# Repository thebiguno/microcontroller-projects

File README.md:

microcontroller-projects
========================

A home for my microcontroller projects, including Stubby the Hexapod and others.  It includes libraries for avr-gcc along with sample programs on how to use them, some KiCad modules, and the source code for a number of projects.

Some major projects include:
 * Stubby the Hexapod (http://stubby.digitalcave.ca/stubby/) (Now extracted into its own repo at https://github.com/thebiguno/stubby)
 * DrumMaster (http://drummaster.digitalcave.ca/drummaster/)
 * Chiindii (http://chiindii.digitalcave.ca/chiindii/)

Some of the AVR libraries included here are:
 * serial communications
 * TWI (I2C), with support for master read / master write / slave read / slave write, plus callback functions for asyncronous communications
 * reading data from a PS2 controller
 * timer functions
 * and much more

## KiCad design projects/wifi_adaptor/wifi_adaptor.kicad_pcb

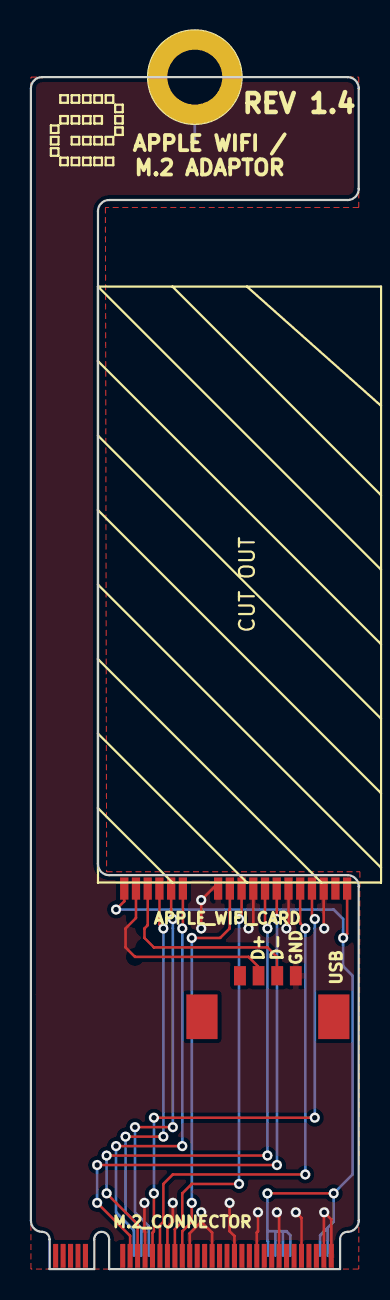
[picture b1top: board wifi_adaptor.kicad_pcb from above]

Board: 2 copper layers, 22.0 x 80.0 mm, 5 parts (0 on the bottom side), 13 nets.

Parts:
J1: APPLE_WIFI_CARD
J2: m.2_connector; M.2_CONNECTOR
MP1: MOUNTING_HOLE; MOUNTING_HOLE_#6
MP2: GRAPHIC; DIGITALCAVE_LOGO
P1: USB; Pin_Header_Straight_1x04

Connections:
+3V3: J1.1, J1.18, J2.2, J2.4, J2.12, J2.14, J2.16, J2.18
GND: J1.3, J1.6, J1.9, J1.12, J2.1, J2.3, J2.9, J2.15, J2.21, J2.27, J2.33, J2.39, J2.45, J2.51, MP1.1, P1.4
unnamed: J1.4, J2.49
unnamed: J1.5, J2.47
unnamed: J1.7, J2.55
unnamed: J1.8, J2.53
unnamed: J1.10, J2.43
unnamed: J1.11, J2.41
unnamed: J1.13, J2.54
unnamed: J1.14, J2.50
unnamed: J1.15, J2.52
unnamed: J1.16, P1.3
unnamed: J1.17, P1.2

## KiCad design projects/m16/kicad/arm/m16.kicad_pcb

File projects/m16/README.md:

https://esdblog.org/how-to-drive-4096-rgb-leds-each-24bit-rgb-brightness-with-one-stm32-microcontroller-without-much-cpu-load/

4-bits per pixel, expanding to 16-bit per pixel for gamma adjustment
see http://www.batsocks.co.uk/readme/p_art_bcm.htm
0     0
1    17/32767 = 0.0005%
2   116
3   362
4   809
5  1512
6  2519
7  3878
8  5637
9  7839
a 10529
b 13749
c 17542
d 21949
e 27011
f 32767

64x32 matrix w/ 1/16 scan rate
2048 rgb leds, 16 * 128 rgb rows

3072 byte frame buffer ?
dma buffer: [x:x:x:b1:g1:r1:ck:b0:g0:r0:oe:st:d:c:b:a] ?
2 rgb leds per dma value
64 dma values per row
16384 16-bit dma values per frame

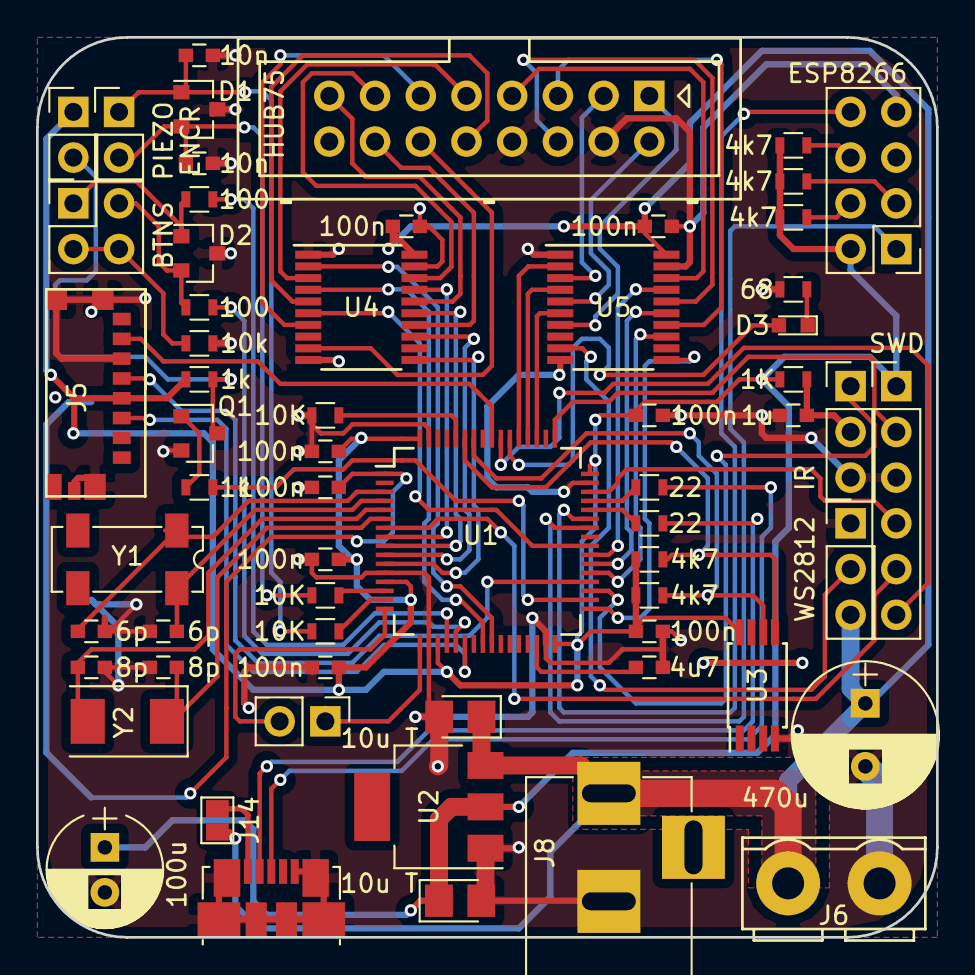
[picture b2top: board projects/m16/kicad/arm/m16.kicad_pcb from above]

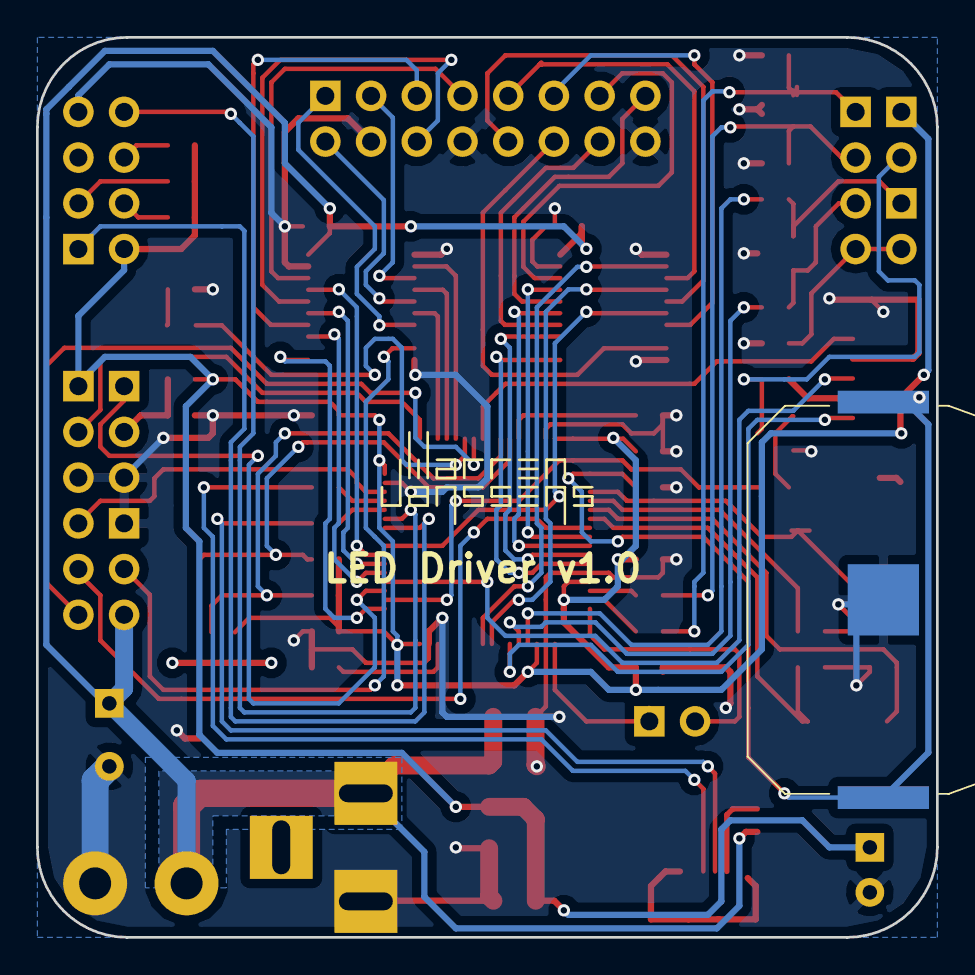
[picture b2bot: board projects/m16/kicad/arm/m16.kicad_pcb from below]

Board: 2 copper layers, 50.0 x 50.0 mm, 64 parts (2 on the bottom side), 75 nets.

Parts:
BT1: 2032 3V; Keystone_3034_1x20mm-CoinCell
C1, C3: 10n; C_0603
C2, C4, C8, C9, C10, C11, C12, C17: 100n; C_0603
C5, C7: 6p; C_0603
C6: 4u7; C_0603
C13: 470u; CP_Radial_D8.0mm_P3.50mm
C14, C16: 10u T; CP_Tantalum_Case-R_EIA-2012-12_Reflow
C15: 1u; C_0603
C18: 100u; CP_Radial_D6.3mm_P2.50mm
C19, C20: 8p; C_0603
D1, D2: D_TVS_x2_AAC; SOT-23
D3: LED; LED_0603
J1: ENCR; Pin_Header_Straight_1x02_Pitch2.54mm
J2: SWD; Pin_Header_Straight_1x06_Pitch2.54mm
J3: BTNS; Pin_Header_Straight_2x02_Pitch2.54mm
J4: ESP8266; Pin_Header_Straight_2x04_Pitch2.54mm
J5: Molex 475710001; 475710001
J6: Conn_01x02; SCREW_TERMINAL_2
J7: HUB75; Multicomp_MC9A12-1634_2x08x2.54mm_Straight
J8: POWER; BARREL_JACK
J9: PIEZO; Pin_Header_Straight_1x02_Pitch2.54mm
J10: IR; Pin_Header_Straight_1x03_Pitch2.54mm
J11: WS2812; Pin_Header_Straight_1x03_Pitch2.54mm
J12: USB_OTG; USB_Micro-B_Molex_47346-0001
J13: SERIAL; Pin_Header_Straight_1x02_Pitch2.54mm
J14: GS2
Q1: MMBT3904; SOT-23
R1, R3, R9: 10K; R_0603
R2, R4: 1k; R_0603
R5, R15: 100; R_0603
R6, R7, R8, R13, R14: 4k7; R_0603
R10: 68; R_0603
R11: 1K; R_0603
R12, R17: 22; R_0603
R16: 10k; R_0603
U1: STM32F411RETx; LQFP-64_10x10mm_Pitch0.5mm
U2: LM1117-3.3; SOT-223
U3: 24LC16; TSSOP-8_4.4x3mm_Pitch0.65mm
U4, U5: 74HCT244; TSSOP-20_4.4x6.5mm_Pitch0.65mm
WJ20: VAL**; WJ20
Y1: ABS25-32.768-6; Crystal_SMD_SeikoEpson_MC306-4pin_8.0x3.2mm
Y2: 16MHz; Crystal_SMD_0603-2pin_6.0x3.5mm

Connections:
+3V3: C8.2, C9.2, C10.2, C11.2, C12.2, C16.1, C18.1, J2.1, J4.2, J5.4, J9.1, R4.1, R6.1, R7.1, R8.1, R11.2, R13.1, R14.2, U1.13, U1.19, U1.32, U1.48, U1.64, U2.2, U3.8
+5V: C2.2, C13.1, C14.1, C17.2, J6.1, J8.1, J11.3, J14.2, U2.3, U4.20, U5.20
+BATT: BT1.1, C4.1, U1.1
/EN1_A: R3.2, U1.14
/EN1_B: R1.2, U1.15
/ESP_EN: J4.6, R8.2
/ESP_RX: J4.1, U1.42
/ESP_TX: J4.8, U1.43
/HSE_N: C19.1, U1.6, Y2.1
/HSE_P: C20.1, U1.5, Y2.2
/IDC_A: J7.9, U4.3
/IDC_B: J7.10, U4.5
/IDC_B0: J7.3, U5.3
/IDC_B1: J7.7, U5.18
/IDC_C: J7.11, U4.7
/IDC_CLK: J7.13, U4.18
/IDC_D: J7.12, U4.9
/IDC_G0: J7.2, U5.5
/IDC_G1: J7.6, U5.16
/IDC_OE: J7.15, U4.16
/IDC_R0: J7.1, U5.7
/IDC_R1: J7.5, U5.14
/IDC_STB: J7.14, U4.14
/IR_DO: J10.1, U1.35
/IR_VS: C15.2, J10.2, R11.1
/JTCK: J2.2, U1.49
/JTMS: J2.4, U1.46
/LED: D3.2, U1.54
/LSE_N: C7.1, U1.4, Y1.4
/LSE_P: C5.1, U1.3, Y1.1
/NRST: J2.5, U1.7
/PZ_DO: R2.1, U1.34
/RGB_A: U1.8, U4.17
/RGB_B: U1.9, U4.15
/RGB_B0: U1.39, U5.17
/RGB_B1: U1.53, U5.2
/RGB_C: U1.10, U4.13
/RGB_CLK: U1.25, U4.2
/RGB_D: U1.11, U4.11
/RGB_G0: U1.38, U5.15
/RGB_G1: U1.52, U5.4
/RGB_OE: U1.24, U4.4
/RGB_R0: U1.37, U5.13
/RGB_R1: U1.51, U5.6
/RGB_STB: U1.40, U4.6
/RX: J13.1, U1.17
/SCL: R14.1, U1.58, U3.6
/SDA: R13.2, U1.59, U3.5
/SDIO_CK: J5.5, U1.36
/SDIO_CMD: J5.3, U1.22
/SDIO_D0: J5.7, U1.56
/SW1: R5.1, U1.20
/SW2: R15.1, U1.21
/SWO: J2.6, U1.55
/TX: J13.2, U1.16
/USB_DM: R17.2, U1.44
/USB_DP: R12.2, U1.45
/WS_DI: J11.2, U5.9
/WS_DO: U1.33, U5.11
GND: BT1.2, C1.1, C2.1, C3.1, C4.2, C5.2, C6.2, C7.2, C8.1, C9.1, C10.1, C11.1, C12.1, C13.2, C14.2, C15.1, C16.2, C17.1, C18.2, C19.2, C20.2, D1.3, D2.3, J2.3, J4.7, J5.6, J5.9, J5.10, J5.11, J5.12, J6.2, J7.4, J7.8, J7.16, J8.2, J10.3, J11.1, J12.5, J12.6, Q1.2, R9.2, R10.2, R16.1, U1.12, U1.18, U1.31, U1.47, U1.63, U2.1, U3.4, U4.1, U4.10, U4.19, U5.1, U5.10, U5.19
unnamed: C1.2, D1.1, J1.1, R1.1
unnamed: C3.2, D1.2, J1.2, R3.1
unnamed: C6.1, U1.30
unnamed: D2.1, J3.1, R5.2
unnamed: D2.2, J3.2, R15.2
unnamed: D3.1, R10.1
unnamed: J3.3, J3.4, R16.2
unnamed: J4.3, R6.2
unnamed: J4.4, R7.2
unnamed: J9.2, Q1.3, R4.2
unnamed: J12.1, J14.1
unnamed: J12.2, R17.1
unnamed: J12.3, R12.1
unnamed: Q1.1, R2.2
unnamed: R9.1, U1.60

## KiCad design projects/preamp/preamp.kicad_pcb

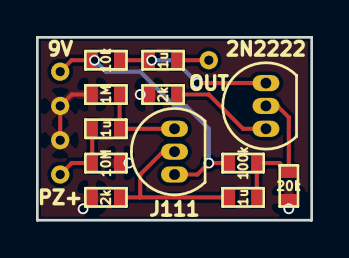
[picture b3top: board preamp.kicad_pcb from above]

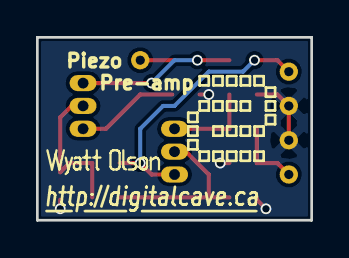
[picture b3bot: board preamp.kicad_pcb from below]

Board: 2 copper layers, 15.2 x 10.2 mm, 18 parts (3 on the bottom side), 9 nets.

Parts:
C1, C2, C3: 1u; SM0603_VALUE
MP1: GRAPHIC; DIGITALCAVE_AUTHOR
MP2: GRAPHIC; DIGITALCAVE_LOGO
MP3: GRAPHIC; DIGITALCAVE_URL
P1: PZ+; Pin_Header_Straight_1x02
P2: 9V; Pin_Header_Straight_1x02
P4: OUT; Pin_Header_Straight_1x01
Q1: J111; TO-92_Inline_Narrow_Oval
Q2: 2N2222; TO-92_Inline_Narrow_Oval
R1: 10M; SM0603_VALUE
R2: 1M; SM0603_VALUE
R3, R7: 2k; SM0603_VALUE
R4: 100k; SM0603_VALUE
R5: 20k; SM0603_VALUE
R6: 10k; SM0603_VALUE

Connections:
+BATT: P2.1, Q1.1, R4.1, R6.1
GND: P1.2, P2.2, R1.2, R2.2, R3.2, R5.2, R7.2
unnamed: C1.1, Q1.3, R2.1
unnamed: C1.2, P1.1, R1.1
unnamed: C2.1, Q2.2, R4.2, R5.1
unnamed: C2.2, Q1.2, R3.1
unnamed: C3.1, P4.1
unnamed: C3.2, Q2.3, R6.2
unnamed: Q2.1, R7.1

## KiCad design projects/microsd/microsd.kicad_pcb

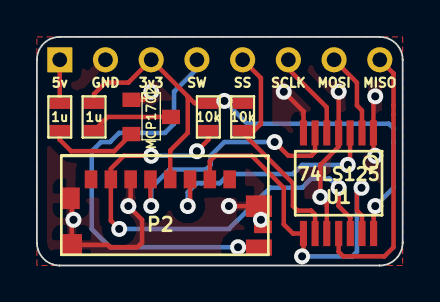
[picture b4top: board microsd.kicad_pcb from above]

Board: 2 copper layers, 20.3 x 12.7 mm, 8 parts (0 on the bottom side), 14 nets.

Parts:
C1, C2: 1u; SM0603_VALUE
P1: CONN_8; SIL-8
P2: CONN_13; 475710001
R1, R2: 10k; SM0603_VALUE
U1: 74LS125; SSOP-14
VR1: MCP1702; SOT23

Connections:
/5V: C2.2, P1.1
/CLK: P2.5, U1.6
/CS: P2.2, U1.8, U1.13
/DET: P1.4, P2.13
/DI: P2.3, U1.3
/DO: P2.7, R1.1, U1.12
/MISO: P1.8, U1.11
/MOSI: P1.7, U1.2
/SCLK: P1.6, U1.5
/SS: P1.5, R2.2, U1.9
GND: P1.2, P2.6, P2.9, P2.10, P2.11, P2.12, U1.1, U1.4, U1.7, U1.10, VR1.1
unnamed: C2.1, VR1.2
unnamed: C1.1, VR1.3
VCC: C1.2, P1.3, P2.4, R1.2, R2.1, U1.14

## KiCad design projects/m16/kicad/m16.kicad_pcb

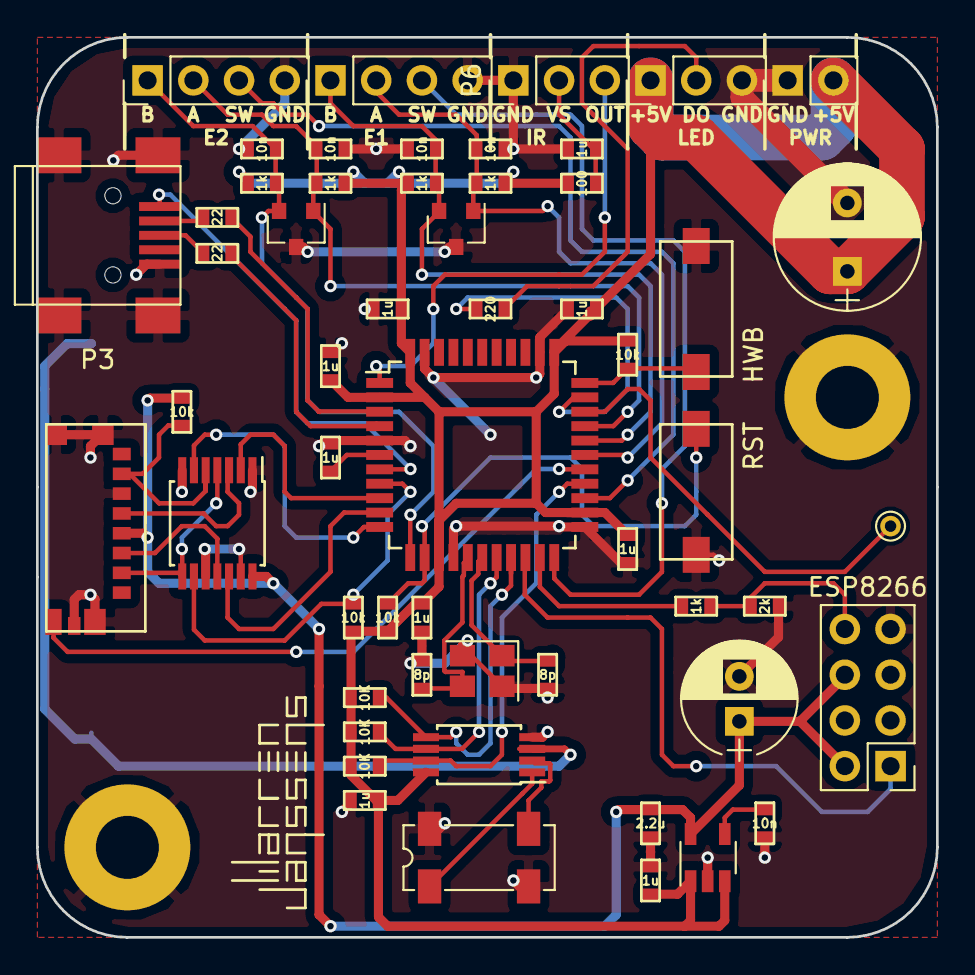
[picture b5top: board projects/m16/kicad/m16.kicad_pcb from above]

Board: 2 copper layers, 50.0 x 50.0 mm, 59 parts (1 on the bottom side), 43 nets.

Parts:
BT1: 3V; Keystone_3034_1x20mm-CoinCell
C1, C2, C3, C4, C19: 10n; SM0603_VALUE
C5, C6: 8p; SM0603_VALUE
C7, C8, C9, C10, C11, C12, C13, C15, C18: 1u; SM0603_VALUE
C14: 470u; CP_Radial_D8.0mm_P3.80mm
C16: 100u; CP_Radial_D6.3mm_P2.50mm
C17: 2.2u; SM0603_VALUE
D1, D2: TVS; SOT-23
J2: TEST_1P; PINTST
MP1, MP2: MOUNTING_HOLE; MountingHole_3.5mm_Pad
P1: ENC1; Pin_Header_Straight_1x04_Pitch2.54mm
P2: ENC2; Pin_Header_Straight_1x04_Pitch2.54mm
P3: USB_OTG; USB_Mini-B
P4: Molex 475710001; 475710001
P5: PWR; Pin_Header_Straight_1x02_Pitch2.54mm
P6: IR; Pin_Header_Straight_1x03_Pitch2.54mm
P7: ESP8266; Pin_Header_Straight_2x04_Pitch2.54mm
P8: WS2812; Pin_Header_Straight_1x03_Pitch2.54mm
R1, R2, R3, R4, R14: 1k; SM0603_VALUE
R5, R6, R7, R11: 10k; SM0603_VALUE
R8, R9: 22; SM0603_VALUE
R10, R12, R13: 10K; SM0603_VALUE
R15: 2k; SM0603_VALUE
R16: 220; SM0603_VALUE
R17: 100; SM0603_VALUE
SW1: RST; SW_6x3
SW2: HWB; SW_6x3
U1: 74LS125; TSSOP-14_4.4x5mm_Pitch0.65mm
U2: ATMEGA32U4-A; TQFP-44_10x10mm_Pitch0.8mm
U3: MCP7941X; TSSOP-8_4.4x3mm_Pitch0.65mm
U4: MIC5219-3.3BM5; TSOT-23-5
WJ20: VAL**; WJ20
X1: 16M 8p; Crystal_SMD_3225-4pin_3.2x2.5mm
X2: 32.768k 6-9p; Crystal_SMD_SeikoEpson_MC306-4pin_8.0x3.2mm

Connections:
+3V3: C16.1, C17.1, P4.4, P7.2, P7.6, R5.1, U1.14, U4.5
+5V: C8.1, C9.1, C10.1, C11.1, C12.1, C13.1, C14.1, C15.1, P5.2, P8.1, R1.2, R2.2, R3.2, R4.2, R6.1, R7.1, R10.1, R11.2, R12.1, R13.1, R17.2, U2.2, U2.14, U2.24, U2.34, U2.44, U3.8, U4.1, U4.3
+BATT: BT1.1, U3.3
/CLK: P4.5, U1.3
/CS: P4.2, U1.4, U1.8
/D+: R8.2, U2.4
/D-: R9.2, U2.3
/DET: P4.13, U2.27
/DI: P4.3, U1.11
/DN: P3.2, R9.1
/DO: P4.7, R5.2, U1.5
/DP: P3.3, R8.1
/E1A: C1.2, D1.1, P1.2, R1.1, U2.28
/E1B: C3.2, D1.2, P1.1, R3.1, U2.29
/E1S: P1.3, U2.22
/E2A: C2.2, D2.1, P2.2, R2.1, U2.30
/E2B: C4.2, D2.2, P2.1, R4.1, U2.12
/E2S: P2.3, U2.25
/HWB: R11.1, SW2.1, U2.33
/IROUT: P6.3, U2.1
/LED: R16.2, U2.32
/MFP: R13.2, U2.26, U3.7
/MISO: U1.6, U2.11
/MOSI: U1.12, U2.10
/RST: R7.2, SW1.2, U2.13
/RX_TX: P7.1, U2.20
/SCL: R10.2, U2.18, U3.6
/SCLK: U1.2, U2.9
/SDA: R12.2, U2.19, U3.5
/SS: R6.2, U1.9, U2.8
/TX_RX: R14.2, U2.21
/VBUS: P3.1, U2.7
/X+: C5.2, U2.17, X1.1
/X-: C6.2, U2.16, X1.3
/Y+: U3.1, X2.1
/Y-: U3.2, X2.3
GND: BT1.2, C1.1, C2.1, C3.1, C4.1, C5.1, C6.1, C7.1, C8.2, C9.2, C10.2, C11.2, C12.2, C13.2, C14.2, C15.2, C16.2, C17.2, C18.1, C19.2, D1.3, D2.3, MP1.1, MP2.1, P1.4, P2.4, P3.5, P3.6, P4.6, P4.9, P4.10, P4.11, P4.12, P5.1, P6.1, P7.7, P8.3, R15.1, SW1.1, SW2.2, U1.1, U1.7, U1.10, U1.13, U2.5, U2.15, U2.23, U2.35, U2.43, U3.4, U4.2, X1.2, X1.4, X2.2, X2.4
unnamed: C7.2, U2.6
unnamed: C18.2, P6.2, R17.1
unnamed: C19.1, U4.4
unnamed: J2.1, U2.31
unnamed: P7.8, R14.1, R15.2
unnamed: P8.2, R16.1

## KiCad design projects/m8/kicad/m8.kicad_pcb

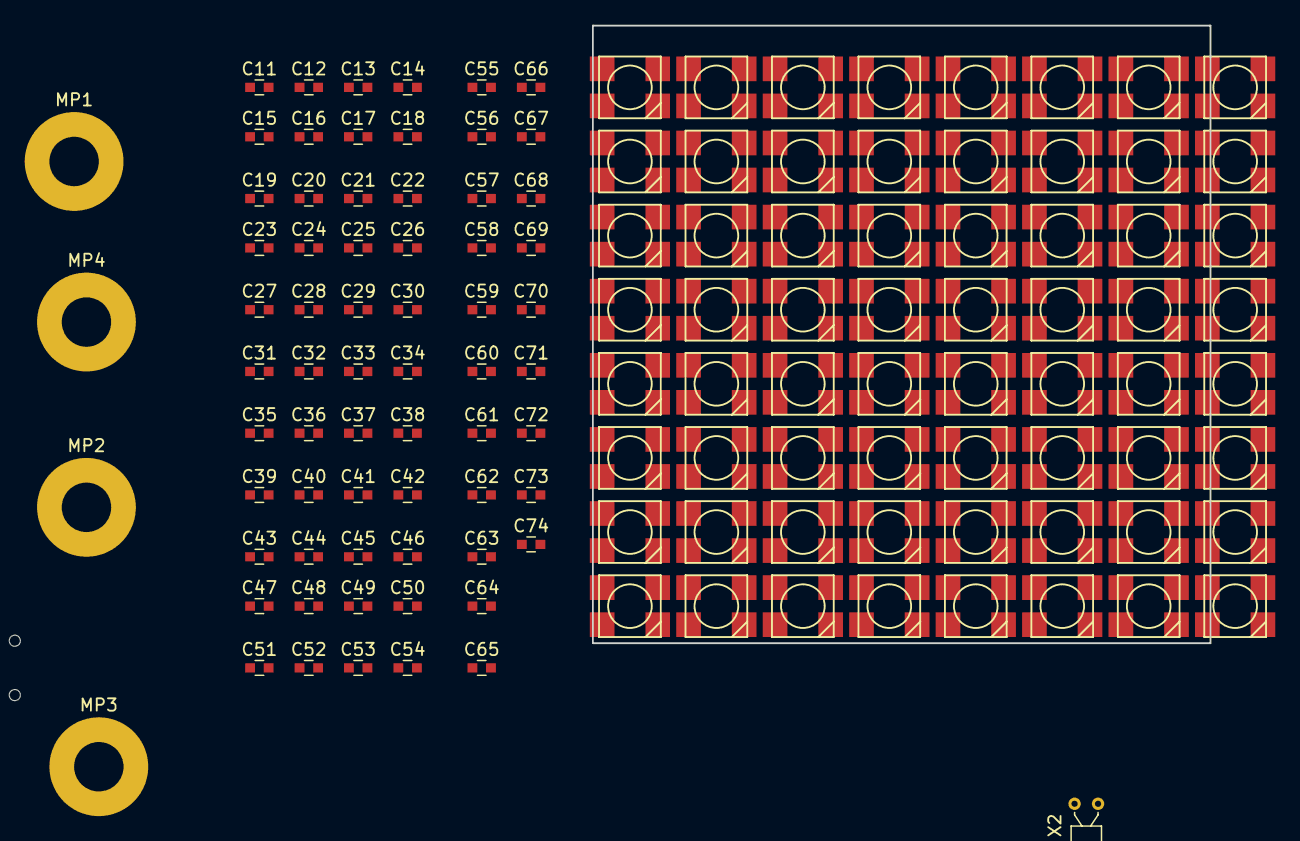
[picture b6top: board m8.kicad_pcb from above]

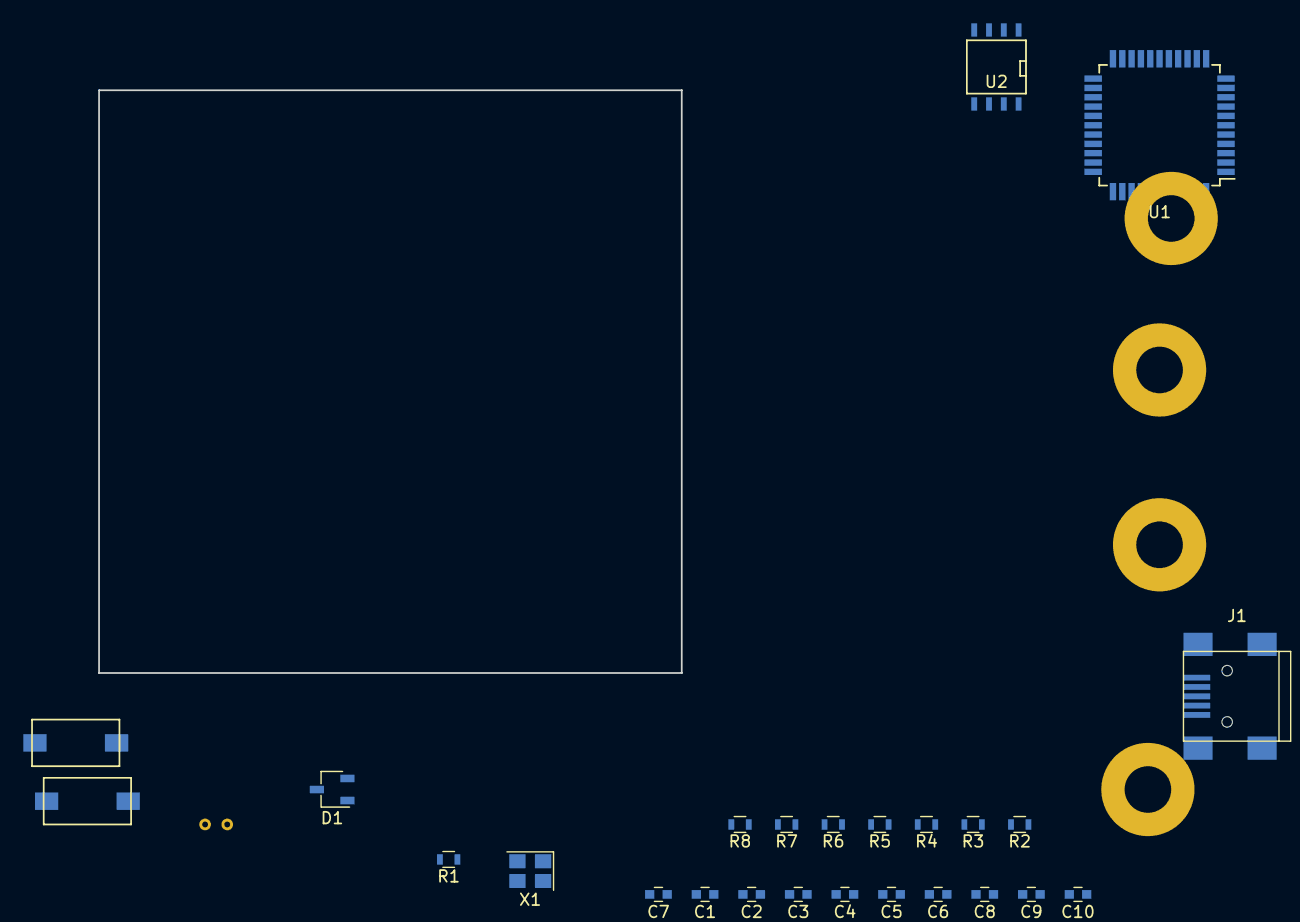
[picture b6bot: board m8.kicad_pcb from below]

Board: 2 copper layers, 50.0 x 50.0 mm, 158 parts (25 on the bottom side), 83 nets, no tracks yet.

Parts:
C1, C2: 12pF; C_0603
C3: 1uF; C_0603
C4, C11, C12, C13, C14, C15, C16, C17, C18, C19, C20, C21, C22, C23, C24, C25, C26, C27, C28, C29, C30, C31, C32, C33, C34, C35, C36, C37, C38, C39, C40, C41, C42, C43, C44, C45, C46, C47, C48, C49, C50, C51, C52, C53, C54, C55, C56, C57, C58, C59, C60, C61, C62, C63, C64, C65, C66, C67, C68, C69, C70, C71, C72, C73, C74: 0.1uF; C_0603
C5, C6, C7, C8, C9, C10: .1 uF; C_0603
D1: TVS_BIDIRECTIONAL_2CH; TSOT-23
J1: USB_OTG; USB_Mini-B
MP1, MP2, MP3, MP4: MOUNTING_HOLE; MountingHole_4mm_Pad
R1, R2: 22; R_0603
R3, R4: 4k7; R_0603
R5, R6, R7, R8: 10k; R_0603
SW3: HWB; SW_6x3
SW4: RST; SW_6x3
U1: ATMEGA32U4-AU; TQFP-44_10x10mm_Pitch0.8mm
U2: MCP7940N; SOIC-8-N
U3, U4, U5, U6, U7, U8, U9, U10, U11, U12, U13, U14, U15, U16, U17, U18, U19, U20, U21, U22, U23, U24, U25, U26, U27, U28, U29, U30, U31, U32, U33, U34, U35, U36, U37, U38, U39, U40, U41, U42, U43, U44, U45, U46, U47, U48, U49, U50, U51, U52, U53, U54, U55, U56, U57, U58, U59, U60, U61, U62, U63, U64, U65, U66: WS2812; SK6812
X1: 16 MHz 12pF; Crystal_SMD_3225-4pin_3.2x2.5mm
X2: 32.768 kHz 12pF; Crystal_C26-LF_d2.1mm_l6.5mm_Horizontal

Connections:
/DI: U1.10, U3.4
/HWB: R7.2, SW3.2, U1.33
/MFP: U1.1, U1.26, U1.27, U2.7
/RST: R8.2, SW4.2, U1.13
/SCL: D1.2, R3.1, U1.18, U2.6
/SDA: D1.1, R4.1, U1.19, U2.5
/SW_A: R5.2, U1.41
/SW_B: R6.2, U1.40
/UDM: J1.2, R2.1
/UDP: J1.3, R1.1
GND: C1.2, C2.2, C3.1, C4.1, C5.2, C6.2, C7.2, C8.2, C9.2, C10.2, C11.1, C12.1, C13.1, C14.1, C15.1, C16.1, C17.1, C18.1, C19.1, C20.1, C21.1, C22.1, C23.1, C24.1, C25.1, C26.1, C27.1, C28.1, C29.1, C30.1, C31.1, C32.1, C33.1, C34.1, C35.1, C36.1, C37.1, C38.1, C39.1, C40.1, C41.1, C42.1, C43.1, C44.1, C45.1, C46.1, C47.1, C48.1, C49.1, C50.1, C51.1, C52.1, C53.1, C54.1, C55.1, C56.1, C57.1, C58.1, C59.1, C60.1, C61.1, C62.1, C63.1, C64.1, C65.1, C66.1, C67.1, C68.1, C69.1, C70.1, C71.1, C72.1, C73.1, C74.1, D1.3, J1.5, J1.6, SW3.1, SW4.1, U1.5, U1.15, U1.23, U1.35, U1.43, U2.4, U3.3, U4.3, U5.3, U6.3, U7.3, U8.3, U9.3, U10.3, U11.3, U12.3, U13.3, U14.3, U15.3, U16.3, U17.3, U18.3, U19.3, U20.3, U21.3, U22.3, U23.3, U24.3, U25.3, U26.3, U27.3, U28.3, U29.3, U30.3, U31.3, U32.3, U33.3, U34.3, U35.3, U36.3, U37.3, U38.3, U39.3, U40.3, U41.3, U42.3, U43.3, U44.3, U45.3, U46.3, U47.3, U48.3, U49.3, U50.3, U51.3, U52.3, U53.3, U54.3, U55.3, U56.3, U57.3, U58.3, U59.3, U60.3, U61.3, U62.3, U63.3, U64.3, U65.3, U66.3, X1.2, X1.4
unnamed: C1.1, U1.17, X1.1
unnamed: C2.1, U1.16, X1.3
unnamed: C3.2, U1.6
unnamed: C4.2, U1.42
unnamed: R1.2, U1.4
unnamed: R2.2, U1.3
unnamed: U2.1, X2.2
unnamed: U2.2, X2.1
unnamed: U3.2, U4.4
unnamed: U4.2, U5.4
unnamed: U5.2, U6.4
unnamed: U6.2, U7.4
unnamed: U7.2, U8.4
unnamed: U8.2, U9.4
unnamed: U10.2, U11.4
unnamed: U9.2, U10.4
unnamed: U11.2, U12.4
unnamed: U12.2, U13.4
unnamed: U13.2, U14.4
unnamed: U14.2, U15.4
unnamed: U15.2, U16.4
unnamed: U16.2, U17.4
unnamed: U17.2, U18.4
unnamed: U18.2, U19.4
unnamed: U19.2, U20.4
unnamed: U20.2, U21.4
unnamed: U21.2, U22.4
unnamed: U22.2, U23.4
unnamed: U23.2, U24.4
unnamed: U24.2, U25.4
unnamed: U25.2, U26.4
unnamed: U26.2, U27.4
unnamed: U27.2, U28.4
unnamed: U28.2, U29.4
unnamed: U29.2, U30.4
unnamed: U30.2, U31.4
unnamed: U31.2, U32.4
unnamed: U32.2, U33.4
unnamed: U33.2, U34.4
unnamed: U34.2, U35.4
unnamed: U35.2, U36.4
unnamed: U36.2, U37.4
unnamed: U37.2, U38.4
unnamed: U38.2, U39.4
unnamed: U39.2, U40.4
unnamed: U40.2, U41.4
unnamed: U41.2, U42.4
unnamed: U42.2, U43.4
unnamed: U43.2, U44.4
unnamed: U44.2, U45.4
unnamed: U45.2, U46.4
unnamed: U46.2, U47.4
unnamed: U47.2, U48.4
unnamed: U48.2, U49.4
unnamed: U49.2, U50.4
unnamed: U50.2, U51.4
unnamed: U51.2, U52.4
unnamed: U52.2, U53.4
unnamed: U53.2, U54.4
unnamed: U54.2, U55.4
unnamed: U55.2, U56.4
unnamed: U56.2, U57.4
unnamed: U57.2, U58.4
unnamed: U58.2, U59.4
unnamed: U59.2, U60.4
unnamed: U60.2, U61.4
unnamed: U61.2, U62.4
unnamed: U62.2, U63.4
unnamed: U63.2, U64.4
unnamed: U64.2, U65.4
unnamed: U65.2, U66.4
VCC: C5.1, C6.1, C7.1, C8.1, C9.1, C10.1, C11.2, C12.2, C13.2, C14.2, C15.2, C16.2, C17.2, C18.2, C19.2, C20.2, C21.2, C22.2, C23.2, C24.2, C25.2, C26.2, C27.2, C28.2, C29.2, C30.2, C31.2, C32.2, C33.2, C34.2, C35.2, C36.2, C37.2, C38.2, C39.2, C40.2, C41.2, C42.2, C43.2, C44.2, C45.2, C46.2, C47.2, C48.2, C49.2, C50.2, C51.2, C52.2, C53.2, C54.2, C55.2, C56.2, C57.2, C58.2, C59.2, C60.2, C61.2, C62.2, C63.2, C64.2, C65.2, C66.2, C67.2, C68.2, C69.2, C70.2, C71.2, C72.2, C73.2, C74.2, J1.1, R3.2, R4.2, R5.1, R6.1, R7.1, R8.1, U1.2, U1.7, U1.14, U1.24, U1.34, U1.44, U2.8, U3.1, U4.1, U5.1, U6.1, U7.1, U8.1, U9.1, U10.1, U11.1, U12.1, U13.1, U14.1, U15.1, U16.1, U17.1, U18.1, U19.1, U20.1, U21.1, U22.1, U23.1, U24.1, U25.1, U26.1, U27.1, U28.1, U29.1, U30.1, U31.1, U32.1, U33.1, U34.1, U35.1, U36.1, U37.1, U38.1, U39.1, U40.1, U41.1, U42.1, U43.1, U44.1, U45.1, U46.1, U47.1, U48.1, U49.1, U50.1, U51.1, U52.1, U53.1, U54.1, U55.1, U56.1, U57.1, U58.1, U59.1, U60.1, U61.1, U62.1, U63.1, U64.1, U65.1, U66.1

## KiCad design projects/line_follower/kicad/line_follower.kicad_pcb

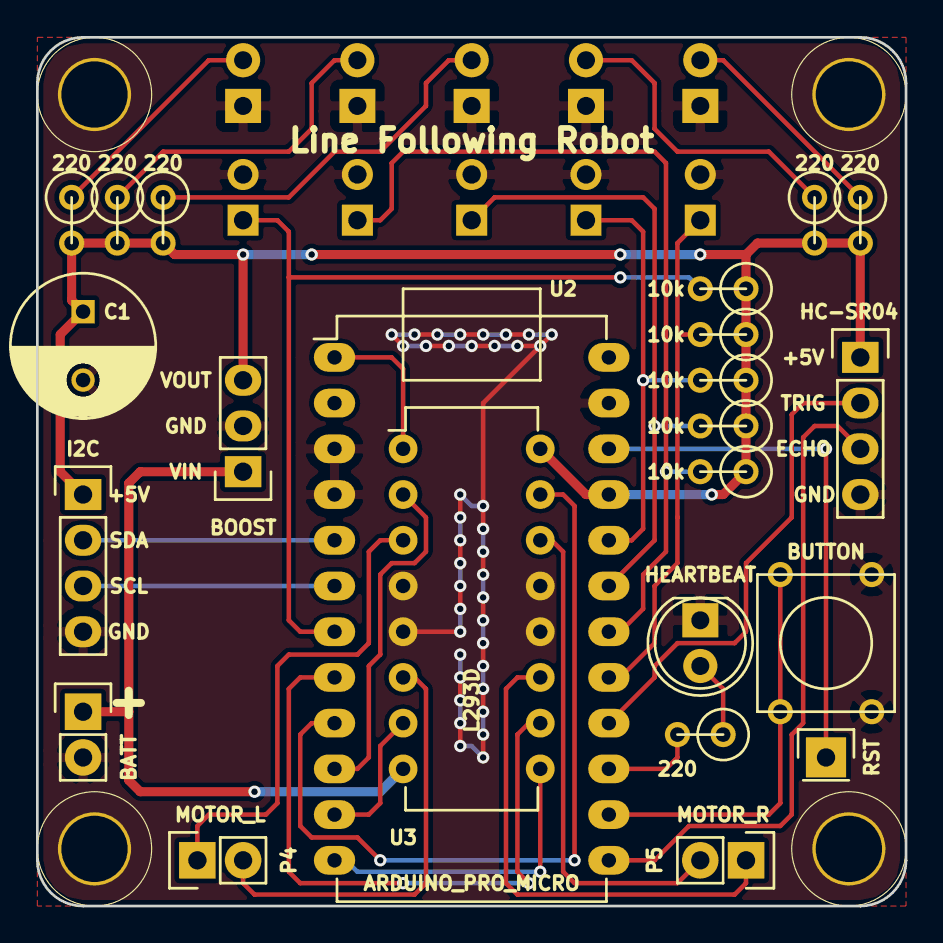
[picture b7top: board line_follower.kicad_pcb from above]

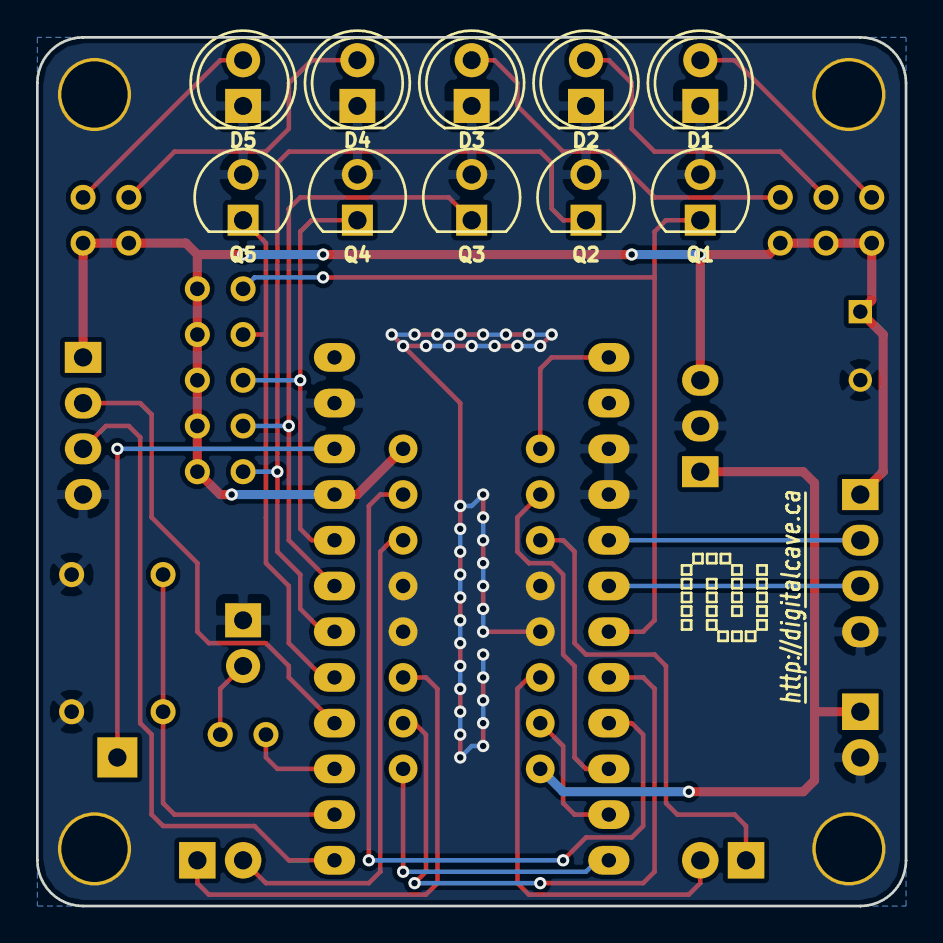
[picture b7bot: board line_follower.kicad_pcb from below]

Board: 2 copper layers, 48.3 x 48.3 mm, 39 parts (12 on the bottom side), 31 nets.

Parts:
C1: CAP; C_Radial_D8_L13_P3.8
D1, D2, D3, D4, D5: IR_LED; LED-5MM
D6: HEARTBEAT; LED-5MM
MP1, MP2, MP3, MP4: MOUNTING_HOLE; MOUNTING_HOLE_#6
MP5: GRAPHIC; DIGITALCAVE_LOGO
MP6: GRAPHIC; DIGITALCAVE_URL
P1: I2C; Pin_Header_Straight_1x04
P2: RST; Pin_Header_Straight_1x01
P3: HC-SR04; Pin_Header_Straight_1x04
P4: MOTOR_L; Pin_Header_Straight_1x02
P5: MOTOR_R; Pin_Header_Straight_1x02
P6: BATT; Pin_Header_Straight_1x02
Q1, Q2, Q3, Q4, Q5: PHOTO_TRANSISTOR; Pin_Header_Angled_2x01
R1, R2, R3, R4, R5, R11: 220; R1
R6, R7, R8, R9, R10: 10k; R1
SW1: BUTTON; SW_PUSH_SMALL
U1: BOOST; Pin_Header_Straight_1x03
U2: ARDUINO_PRO_MICRO; DIP-24_W15.24mm_LongPads
U3: L293D; DIP-16_W7.62mm

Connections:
+5V: C1.1, P1.1, P3.1, R1.2, R2.2, R3.2, R4.2, R5.2, R6.1, R7.1, R8.1, R9.1, R10.1, U1.3, U2.21, U3.16
+BATT: P6.1, U1.1, U3.8
/ADC_1: Q1.1, R7.2, U2.7
/ADC_2: Q2.1, R8.2, U2.18
/ADC_3: Q3.1, R9.2, U2.19
/ADC_4: Q4.1, R10.2, U2.20
/ADC_5: Q5.1, R6.2, U2.17
/DIST_ECHO: P3.3, U2.13
/DIST_TRIG: P3.2, U2.16
/MOTOR_L_1A: U2.10, U3.2
/MOTOR_L_2A: U2.11, U3.7
/MOTOR_L_EN: U2.1, U3.1
/MOTOR_R_3A: U2.8, U3.10
/MOTOR_R_4A: U2.9, U3.15
/MOTOR_R_EN: U2.12, U3.9
/SCL: P1.3, U2.6
/SDA: P1.2, U2.5
GND: C1.2, D1.1, D2.1, D3.1, D4.1, D5.1, D6.1, MP1.1, MP2.1, MP3.1, MP4.1, P1.4, P3.4, P6.2, Q1.2, Q2.2, Q3.2, Q4.2, Q5.2, SW1.1, U1.2, U2.3, U2.4, U2.23, U3.4, U3.5, U3.12, U3.13
unnamed: D1.2, R1.1
unnamed: D2.2, R2.1
unnamed: D3.2, R3.1
unnamed: D4.2, R4.1
unnamed: D5.2, R5.1
unnamed: D6.2, R11.1
unnamed: P2.1, U2.22
unnamed: P4.1, U3.3
unnamed: P4.2, U3.6
unnamed: P5.1, U3.11
unnamed: P5.2, U3.14
unnamed: R11.2, U2.15
unnamed: SW1.2, U2.14

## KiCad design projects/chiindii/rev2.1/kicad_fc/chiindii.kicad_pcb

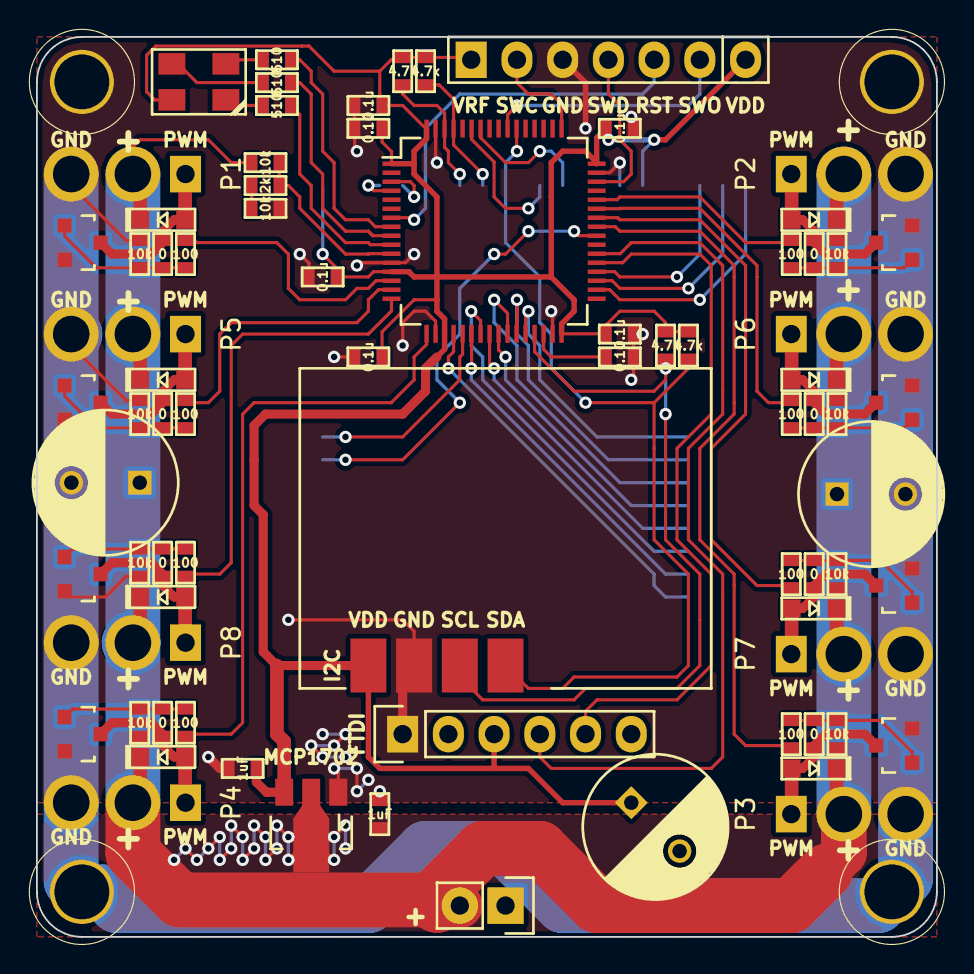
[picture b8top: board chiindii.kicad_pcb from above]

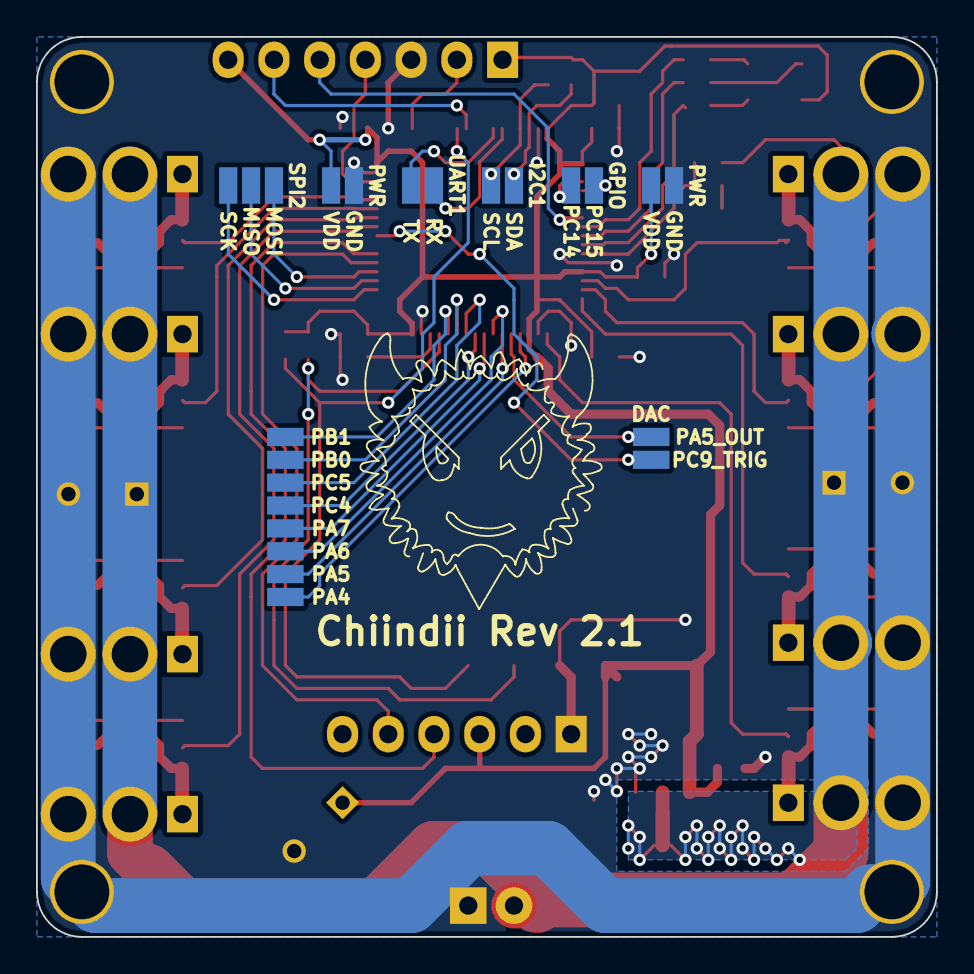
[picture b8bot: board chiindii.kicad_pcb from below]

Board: 2 copper layers, 50.0 x 50.0 mm, 89 parts (8 on the bottom side), 63 nets.

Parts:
C1, C2: 1uF; SM0603_VALUE
C3, C4, C11, C12, C13, C14, C15: 0.1u; SM0603_VALUE
C5, C6, C7: 470uF; C_Radial_D8_L13_P3.8
D1, D2, D3, D4, D5, D6, D7, D8: DSCHSMALL; SOD-323_DIODE
D10: RGB_LED_COMMON_ANODE_ALT1; LED_RGB_4-PLCC_ALT1
MP1, MP2, MP3, MP4: MOUNTING_HOLE; MOUNTING_HOLE_#4
P1, P2, P3, P4, P5, P6, P7, P8: CONN_01X03; Motor_Connector
P9: STLINK; Pin_Header_Straight_1x07
P10: BATTERY; Pin_Header_Straight_1x02
P11: I2C1; Pin_Header_Straight_1x02
P12: UART1; Pin_Header_Straight_1x02
P13: GPIO; Pin_Header_Straight_1x02
P14, P16: PWR; Pin_Header_Straight_1x02
P15: SPI2; Pin_Header_Straight_1x03
P17: CONN_01X08; Pin_Header_Straight_1x08
P18: DAC; Pin_Header_Straight_1x02
P27: FTDI; Pin_Header_Straight_1x06
P33: I2C; Pin_Header_Straight_1x04
Q1, Q2, Q3, Q4, Q5, Q6, Q7, Q8: Q_NMOS_GSD; SOT-23
R1, R2, R7, R8, R13, R14, R34, R35: 100; SM0603_VALUE
R3, R6, R10, R12, R17, R18, R28, R33, R37, R39: 10k; SM0603_VALUE
R4, R5, R9, R11, R15, R32, R36, R38: 0; SM0603_VALUE
R16: 2k; SM0603_VALUE
R19, R23, R24, R27: 4.7k; SM0603_VALUE
R20, R21, R22: 510; SM0603_VALUE
U3: STM32F410; LQFP-64_10x10mm_Pitch0.5mm
VR1: MCP1702; SOT89-3_Housing

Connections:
+3V3: C2.1, C3.2, C5.1, C11.2, C12.2, C13.2, C14.2, C15.2, D10.1, P9.1, P9.7, P14.1, P16.1, P27.3, P33.1, R19.2, R23.2, R24.2, R27.2, U3.1, U3.13, U3.19, U3.32, U3.48, U3.64, VR1.3
+BATT: C1.1, C6.1, C7.1, D1.2, D2.2, D3.2, D4.2, D5.2, D6.2, D7.2, D8.2, P1.2, P2.2, P3.2, P4.2, P5.2, P6.2, P7.2, P8.2, P10.2, R18.2, VR1.2
/BATT_ADC: R16.2, R18.1, U3.11
/I2C1_SCL: P11.1, R23.1, U3.61
/I2C1_SDA: P11.2, R19.1, U3.62
/I2C2_SCL: P33.3, R24.1, U3.29
/I2C2_SDA: P33.4, R27.1, U3.54
/MOTOR1: R1.1, U3.14
/MOTOR2: R2.1, U3.44
/MOTOR3: R7.1, U3.41
/MOTOR4: R8.1, U3.17
/MOTOR5: R13.1, U3.15
/MOTOR6: R14.1, U3.43
/MOTOR7: R34.1, U3.42
/MOTOR8: R35.1, U3.16
/NRST: P9.5, U3.7
/PA4: P17.8, U3.20
/PA5: P18.1, U3.21
/PA6: P17.7, U3.22
/PA7: P17.6, U3.23
/PB0: P17.3, U3.26
/PB1: P17.2, U3.27
/PB2: P17.1, U3.28
/PC4: P17.5, U3.24
/PC5: P17.4, U3.25
/PC9: P18.2, U3.40
/PC14: P13.1, U3.3
/PC15: P13.2, U3.4
/RADIO_RX: P27.5, U3.37
/RADIO_TX: P27.4, U3.38
/SPI2_MISO: P15.2, U3.35
/SPI2_MOSI: P15.1, U3.36
/SPI2_SCK: P15.3, U3.34
/SWCLK: P9.2, U3.49
/SWDIO: P9.4, U3.46
/SWO: P9.6, U3.55
/USART1_RX: P12.1, U3.59
/USART1_TX: P12.2, U3.58
GND: C1.2, C2.2, C3.1, C4.2, C5.2, C6.2, C7.2, C11.1, C12.1, C13.1, C14.1, C15.1, MP1.1, MP2.1, MP3.1, MP4.1, P1.3, P2.3, P3.3, P4.3, P5.3, P6.3, P7.3, P8.3, P9.3, P10.1, P14.2, P16.2, P27.1, P33.2, Q1.2, Q2.2, Q3.2, Q4.2, Q5.2, Q6.2, Q7.2, Q8.2, R3.1, R6.1, R10.1, R12.1, R17.1, R28.1, R33.1, R37.1, R39.1, U3.12, U3.18, U3.31, U3.47, U3.63, VR1.1
unnamed: C4.1, U3.30
unnamed: D1.1, P1.1, Q1.3, R4.2
unnamed: D2.1, P2.1, Q2.3, R5.2
unnamed: D3.1, P3.1, Q3.3, R9.2
unnamed: D4.1, P4.1, Q4.3, R11.2
unnamed: D5.1, P5.1, Q5.3, R15.2
unnamed: D6.1, P6.1, Q6.3, R32.2
unnamed: D7.1, P7.1, Q7.3, R36.2
unnamed: D8.1, P8.1, Q8.3, R38.2
unnamed: D10.2, R22.1
unnamed: D10.3, R21.1
unnamed: D10.4, R20.1
unnamed: Q1.1, R1.2, R3.2, R4.1
unnamed: Q2.1, R2.2, R5.1, R6.2
unnamed: Q3.1, R7.2, R9.1, R10.2
unnamed: Q4.1, R8.2, R11.1, R12.2
unnamed: Q5.1, R13.2, R15.1, R28.2
unnamed: Q6.1, R14.2, R32.1, R33.2
unnamed: Q7.1, R34.2, R36.1, R37.2
unnamed: Q8.1, R35.2, R38.1, R39.2
unnamed: R16.1, R17.2
unnamed: R20.2, U3.8
unnamed: R21.2, U3.9
unnamed: R22.2, U3.10
